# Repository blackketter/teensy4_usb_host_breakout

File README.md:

A companion breakout board with USB-A host connector to mate with the [Teensy 4 Header Breakout Board](https://github.com/blackketter/teensy4_header_breakout).  

It's designed to solder to the top 6 pins on the right side of the Teensy 4 Header Breakout.  

Designed in KiCad.

Notes:

- See also [Combo SD/USB Host breakout](https://github.com/blackketter/teensy4_combo_breakout)
- In progress: First prototype works great.
- With longer header pins you should be able to flip the board to be under or over the Teensy 4.0
- Download bom/ibom.html and view it with web browser to see bill of materials and placement information.
- The 6th pin provides an optional enable pin for the power management chip on digital pin 27.  For always-on, cut left trace and short right two pads.  

Pinout:

1. VUSB
2. USB Host D-
3. USB Host D+
4. GND
5. GND
6. 27/EN

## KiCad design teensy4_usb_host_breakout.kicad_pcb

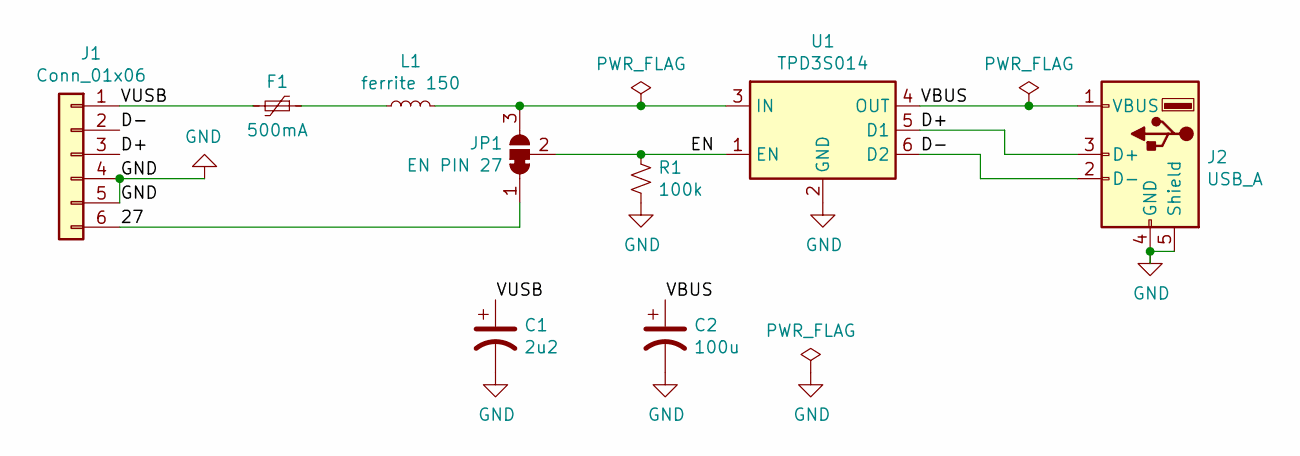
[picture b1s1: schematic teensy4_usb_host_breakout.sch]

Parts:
C1: 2u2; C_0805_2012Metric_Pad1.15x1.40mm_HandSolder; Digikey 1276-1188-1-ND
C2: 100u; C_1206_3216Metric_Pad1.42x1.75mm_HandSolder; Digikey ‎478-12404-1-ND‎
F1: 500mA; L_0805_2012Metric_Pad1.15x1.40mm_HandSolder; Digikey 507-1813-1-ND
J1: Conn_01x06; PinHeader_1x06_P2.54mm_Vertical
J2: USB_A; USB_A_Receptacle_SMD_Wuerth_629104190121; Digikey 732-11179-1-ND
JP1: EN PIN 27; SolderJumper-3_P1.3mm_Bridged12_RoundedPad1.0x1.5mm
L1: ferrite 150; L_0805_2012Metric_Pad1.15x1.40mm_HandSolder; Digikey ‎490-1038-1-ND‎
R1: 100k; R_0805_2012Metric_Pad1.15x1.40mm_HandSolder; Digikey 311-100KCRCT-ND
U1: TPD3S014; SOT-23-6; Digikey 296-38835-1-ND

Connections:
/27: J1.6, JP1.1 (A)
/D+: J1.3, J2.3 (D+), U1.5 (D1)
/D-: J1.2, J2.2 (D-), U1.6 (D2)
/EN: JP1.2 (C), R1.1, U1.1 (EN)
/VBUS: C2.1, J2.1 (VBUS), U1.4 (OUT)
/VUSB: C1.1, F1.2, J1.1
GND: C1.2, C2.2, J1.4, J1.5, J2.4 (GND), J2.5 (Shield), R1.2, U1.2 (GND)
unnamed: F1.1, L1.1
unnamed: JP1.3 (B), L1.2, U1.3 (IN)

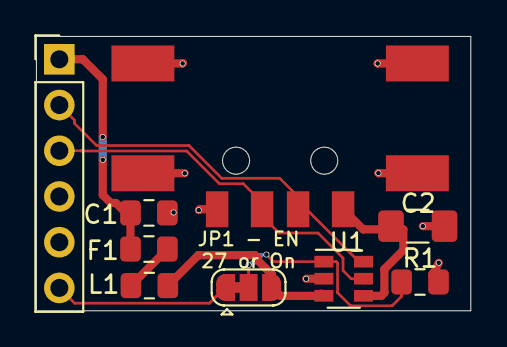
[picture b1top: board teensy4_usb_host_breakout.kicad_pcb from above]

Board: 2 copper layers, 24.1 x 15.2 mm, 9 parts (0 on the bottom side), 9 nets.

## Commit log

2019-09-21 Widened VIN power trace
2019-09-21 Update footprintso
2019-09-22 Update status
2019-09-22 Updated with Digikey part numbers. Removed diodes as TPD3S014DBVR provides reverse voltage protection
2019-09-22 Remove spurious silkscreen lines, update render
2019-09-22 Update schematic PDF
2019-10-05 Updated for jumper for enable (always on vs 27). Also updated docs
2019-12-04 Reference combo breakout
